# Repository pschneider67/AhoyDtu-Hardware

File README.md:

# KiCad 7 - AhoyDtu-Hardware 
A little PCB Board with case for the excellent AhoyDTU software https://ahoydtu.de/.
This little hardware project is to use the AhoyDTU together with a OLED 0.96 display an a 3d printed case.

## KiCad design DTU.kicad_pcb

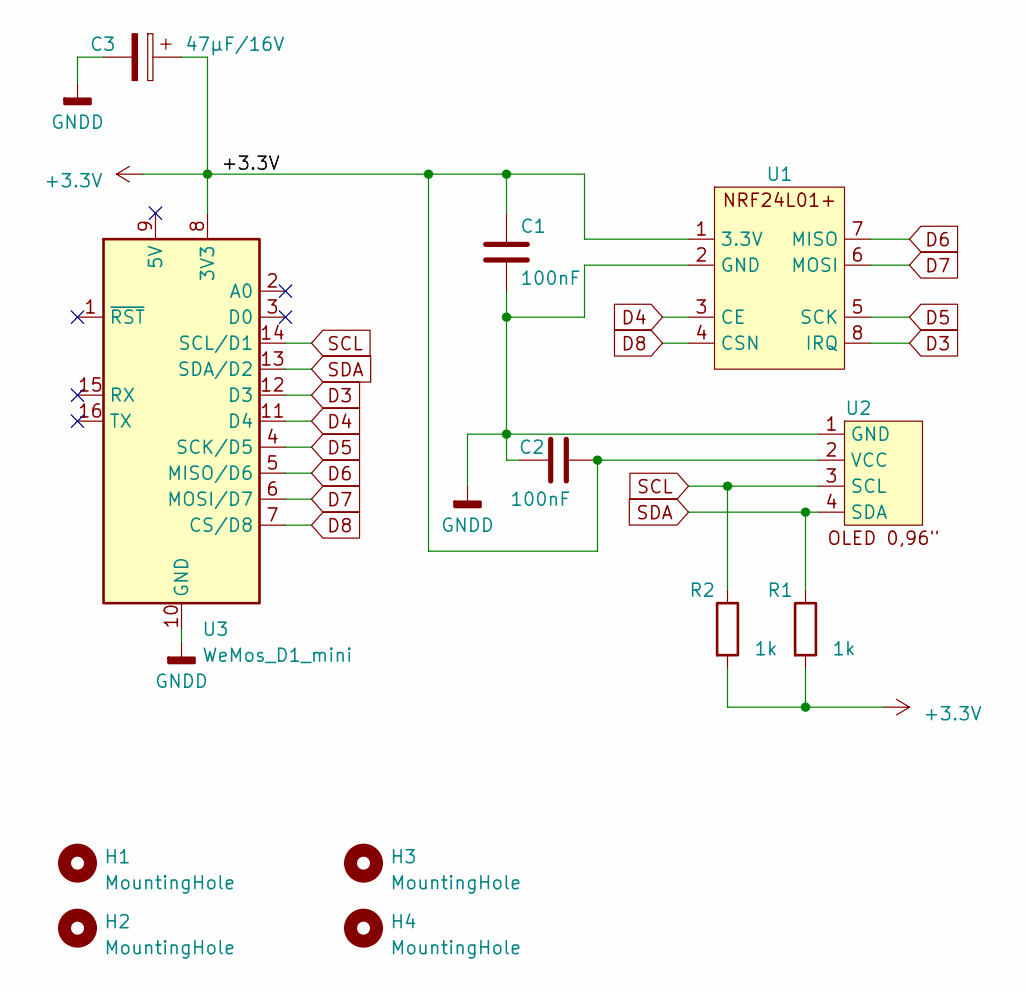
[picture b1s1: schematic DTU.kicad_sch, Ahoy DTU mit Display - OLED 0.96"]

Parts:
C1, C2: 100nF; C_1206_3216Metric_Pad1.33x1.80mm_HandSolder
C3: 47µF/16V; CP_Elec_5x5.3
H1, H2, H3, H4: MountingHole; MountingHole_3.2mm_M3_DIN965_Pad
R1, R2: 1k; R_1206_3216Metric_Pad1.30x1.75mm_HandSolder
U1: NRF24L01+_SMD
U2: OLED_0.96
U3: WeMos_D1_mini; WEMOS_D1_mini_light

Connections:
+3.3V: C1.1, C2.2, C3.1, R1.2, R2.2, U1.1 (3.3V), U2.2 (VCC), U3.8 (3V3)
D3: U1.8 (IRQ), U3.12 (D3)
D4: U1.3 (CE), U3.11 (D4)
D5: U1.5 (SCK), U3.4 (SCK/D5)
D6: U1.7 (MISO), U3.5 (MISO/D6)
D7: U1.6 (MOSI), U3.6 (MOSI/D7)
D8: U1.4 (CSN), U3.7 (CS/D8)
GNDD: C1.2, C2.1, C3.2, U1.2 (GND), U2.1 (GND), U3.10 (GND)
SCL: R2.1, U2.3 (SCL), U3.14 (SCL/D1)
SDA: R1.1, U2.4 (SDA), U3.13 (SDA/D2)

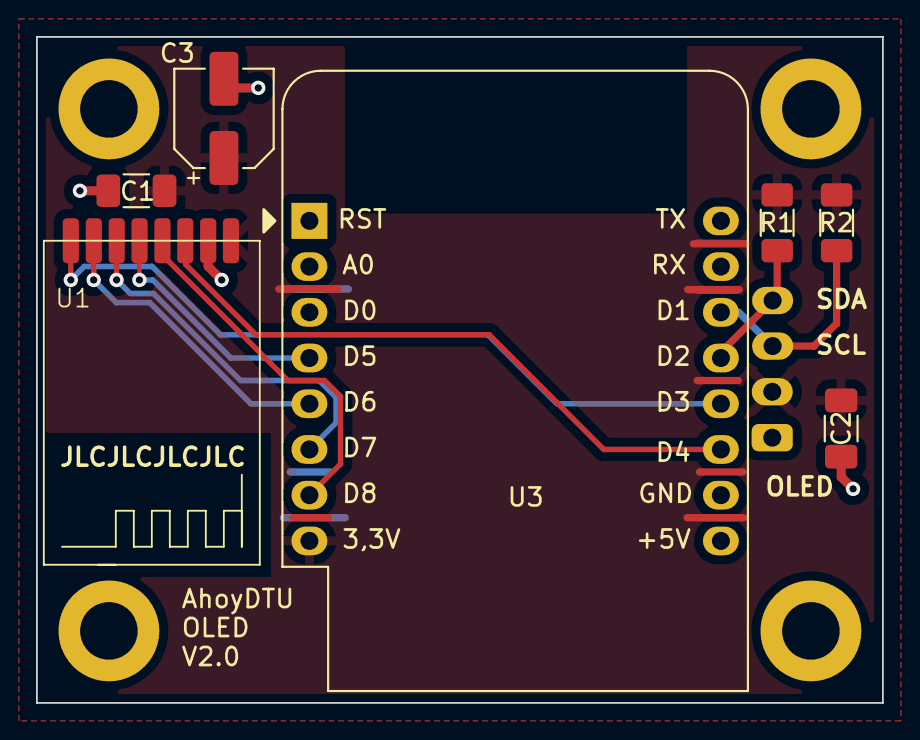
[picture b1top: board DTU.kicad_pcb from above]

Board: 2 copper layers, 47.0 x 37.0 mm, 12 parts (1 on the bottom side), 10 nets.

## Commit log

2023-10-03 Add files via upload
    start GitHub with this little KiCad 7 / FreeCad project
2023-10-03 Add files via upload
    include production files
2023-10-05 add KiCad7 project file
2023-10-05 update case data
